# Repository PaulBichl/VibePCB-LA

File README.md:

# VibePCB logic analyzer

A 16-channel, 100 MSa/s USB 2.0 HS logic analyzer: a **Lattice ECP5 FPGA (CABGA-256 BGA)**
capturing into a **32 MB SDRAM (54-ball BGA)**, read out over an **FT2232H**. 98 x 64 mm, 6 layers.
Designed with [VibePCB](https://github.com/PaulBichl/vibepcb) (tscircuit -> KiCad) as a stretch of
the tooling: two 0.8 mm BGAs escaped and routed by VibePCB's own router, a length-checked 39-signal
memory bus, a coupled 90 ohm USB pair, three power planes.

Status: passes `check` (KiCad DRC and ERC with 0 errors, house rules). Not fabricated yet.

## Look at it

| | |
|---|---|
| Schematic | [PDF](boards/la-ecp5/hardware/la-ecp5-schematic.pdf) |
| Layout | [PDF, one page per copper layer](boards/la-ecp5/hardware/la-ecp5-layout.pdf), [front](boards/la-ecp5/hardware/la-ecp5-layout-front.svg), [back](boards/la-ecp5/hardware/la-ecp5-layout-back.svg) |
| 3D | [top](boards/la-ecp5/hardware/la-ecp5-top.png), [bottom](boards/la-ecp5/hardware/la-ecp5-bottom.png) |
| BOM (LCSC / MPN) | [CSV](boards/la-ecp5/hardware/la-ecp5-bom.csv) |
| KiCad project | [kicad/](boards/la-ecp5/hardware/kicad) |
| Source | [index.circuit.tsx](boards/la-ecp5/index.circuit.tsx) (tscircuit), [vibepcb.toml](boards/la-ecp5/vibepcb.toml) (rules, planes, length groups, BGA escape), [routes.toml](boards/la-ecp5/routes.toml) (routing order) |

The KiCad project opens as it is. The 3D models are left out because they are tens of MB;
`pcb fix` downloads them. Gerbers and pick-and-place files are not in the repo: either plot them
from the KiCad project, or build the board (below) and run `hatch run pcb fab la-ecp5`, which
writes Gerbers, drill, BOM, CPL and a JLCPCB upload set.

## Target spec

| | |
|---|---|
| Channels | 16, two banks of 8, threshold per bank (I/O rail 1.2-5 V, threshold ~ rail / 2) |
| Sample rate | 100 MSa/s x 16 into SDRAM |
| Buffer | 32 MB (256 Mbit 16-bit SDR SDRAM) = 16 M samples x 16 ch |
| Streaming | ~40 MB/s over USB 2.0 HS (FT2232H sync FIFO): 16 ch at ~20 MSa/s |
| Inputs | 1 Mohm, 1k series + SRV05-4 clamps to the bank rail / GND |
| Probe | 2x10 2.54 mm header (16 signals + 4 GND), labelled per pin |
| Power | USB-C 5 V, < 3 W |
| Debug | JTAG header (J5), 3 LEDs (power, activity, trigger) |

## How it works

```
 probe     +--------------+    +---------------+    +-------------+
 header -->| 1k, 1M,      |--->| 74LVC8T245 x2 |--->|             |<--- 100 MHz osc
 16 ch     | SRV05-4      |    | level shift   |    |  ECP5-25F   |
           +--------------+    +---------------+    |  CABGA-256  |<==> IS42S16160J SDRAM
                  ^                    ^            |             |     (32 MB, BGA-54)
                  +--- bank rail ------+            |             |
                       1.2-5 V, x2                  |             |<--- JTAG (J5)
                          ^                         |             |
               TLV9062 + RC filter <------ PWM -----|             |
                                                    +--+-------+--+
                                                       ^       ^
                                    W25Q128 -----------+       | 8-bit sync FIFO
                                    config flash               v
                                       ^  SPI (ch B)     +---------+  USB 2.0 HS  +------------+
                                       +-----------------| FT2232H |<============>| USB-C, ESD |
                                                         +---------+              +-----+------+
                                                                                        | 5 V
                                           3.3 V, 1.1 V, 2.5 V <--- TLV62569 x3 <-------+
```

**Signal path.** A probe signal enters the 2x10 header, passes a 1k series resistor (with the
SRV05-4 clamping it to the bank rail and GND, and 1M pulling an open input low) and reaches a
74LVC8T245. Its A side runs on the bank rail, so the input threshold follows that rail (~ rail / 2);
its B side runs on 3.3 V and drives the FPGA. One translator per bank of 8 channels, so two target
logic families can be probed at once.

**Threshold.** The FPGA sets each bank rail itself: a PWM pin, a 10k / 1 uF RC filter, a TLV9062
op-amp with gain 1.5 -> 1.2 to 4.95 V. No DAC chip needed.

**Capture.** The FPGA samples all 16 inputs at 100 MHz (from the oscillator on a primary clock
input), runs the trigger logic and writes the samples to the SDRAM: 16 bit x 100 MSa/s = 200 MB/s,
which the 16-bit SDRAM (-7 grade, rated to 143 MHz) takes in bursts; 32 MB = 16 M samples (0.16 s at
full rate).

**Readout.** The FT2232H is the USB 2.0 high-speed interface: channel A is an 8-bit synchronous
FIFO to the FPGA (~40 MB/s, its 60 MHz CLKOUT on a primary clock input), enough to read the buffer
out or to stream 16 ch at ~20 MSa/s live. Channel B (MPSSE) writes the FPGA bitstream into the
W25Q128 SPI flash while it holds PROGRAMN low; the FPGA boots from it in master SPI mode
(CFG[2:0] = 010), so no separate programmer is needed. The 93LC56 EEPROM stores the FT2232H's
FIFO-mode setting.

**Power.** USB-C 5 V (5.1k CC pull-downs, no PD) -> three TLV62569 bucks: 3.3 V for I/O, SDRAM and
USB, 1.1 V for the FPGA core, 2.5 V for its aux supply. Under 3 W.

**Why this FPGA.** The ECP5 LFE5U-25F has 24k LUTs, 1 Mbit of block RAM and plenty of I/O for 16
inputs + the 39-signal SDRAM bus + the FIFO, with a fully open toolchain (yosys / nextpnr-ecp5 /
Project Trellis). Its block RAM alone would only hold ~60 k samples, hence the SDRAM. The CABGA-256
package was the point of the exercise: an earlier version of this board used an iCE40HX4K in a
TQFP-144 (4 layers, in git history) because tscircuit's router could not escape a BGA; VibePCB now
does the escape and routing itself.

## Layout

- **Stack-up (6 layers):** top signals + GND / In1 GND / In2 1.1 V core / In3 3.3 V IO /
  In4 GND / bottom signals + GND. Each power ball or pad gets its own via to its plane.
- **BGA escape:** both ball grids are escaped by VibePCB (0.1 mm tracks between the 0.36 mm balls
  at 0.8 mm pitch, dogbone vias 0.4 / 0.2 mm, mechanically drilled; deeper balls out on the
  bottom layer).
- **Planar pin plan:** FPGA pins are assigned by package side so no routes cross: inputs and the
  100 MHz clock west, SDRAM east, FT2232H FIFO north, configuration SPI south. Within a side, signals
  pair with balls by angle around both parts, so the routes nest instead of crossing.
- **SDRAM bus:** two length groups (data, address / control), skew <= 45 mm (~0.3 ns, ~10 % of
  the read window at 100 MHz), checked by KiCad.
- **USB:** a 90 ohm differential pair from the ESD part to the FT2232H, coupled over 7.3 mm with
  +0.09 mm skew.

Net classes, the USB pair, the length groups, the planes and the escape settings live in
[`boards/la-ecp5/vibepcb.toml`](boards/la-ecp5/vibepcb.toml); the routing order in
[`routes.toml`](boards/la-ecp5/routes.toml).

## Parts (JLCPCB / LCSC)

| Part | LCSC |
|------|------|
| LFE5U-25F-7BG256I (FPGA) | C1550762 |
| IS42S16160J-7BLI (SDRAM) | C1348766 |
| FT2232HL (USB) | C27882 |
| SN74LVC8T245PWR | C27643 |
| W25Q128JVSIQ (config flash) | C97521 |
| 93LC56BT-I/OT | C190271 |
| SX3M100.000B20F30TNN (100 MHz osc) | C5179979 |
| X322512MSB4SI (12 MHz crystal) | C9002 |
| TLV62569DBVR | C141836 |
| TLV9062IDR | C398355 |
| USBLC6-2SC6 | C7519 |
| SRV05-4 | C2836319 |
| TYPE-C-31-M-12 | C165948 |

Passives are in the [BOM](boards/la-ecp5/hardware/la-ecp5-bom.csv). Check stock before
ordering.

## Setup / build

Clone [`vibepcb`](https://github.com/PaulBichl/vibepcb) next to this repo as `VibePCB`, then

```bash
hatch run setup
hatch run pcb all la-ecp5       # build, fix, route, check
hatch run pcb publish la-ecp5   # refresh boards/la-ecp5/hardware/
hatch run pcb fab la-ecp5       # Gerbers, drill, BOM, CPL
```

`package.json` pins the tscircuit version the board was built with, because routing differs
between versions.

Out of scope for this repo: FPGA gateware and the host software (a sigrok driver).

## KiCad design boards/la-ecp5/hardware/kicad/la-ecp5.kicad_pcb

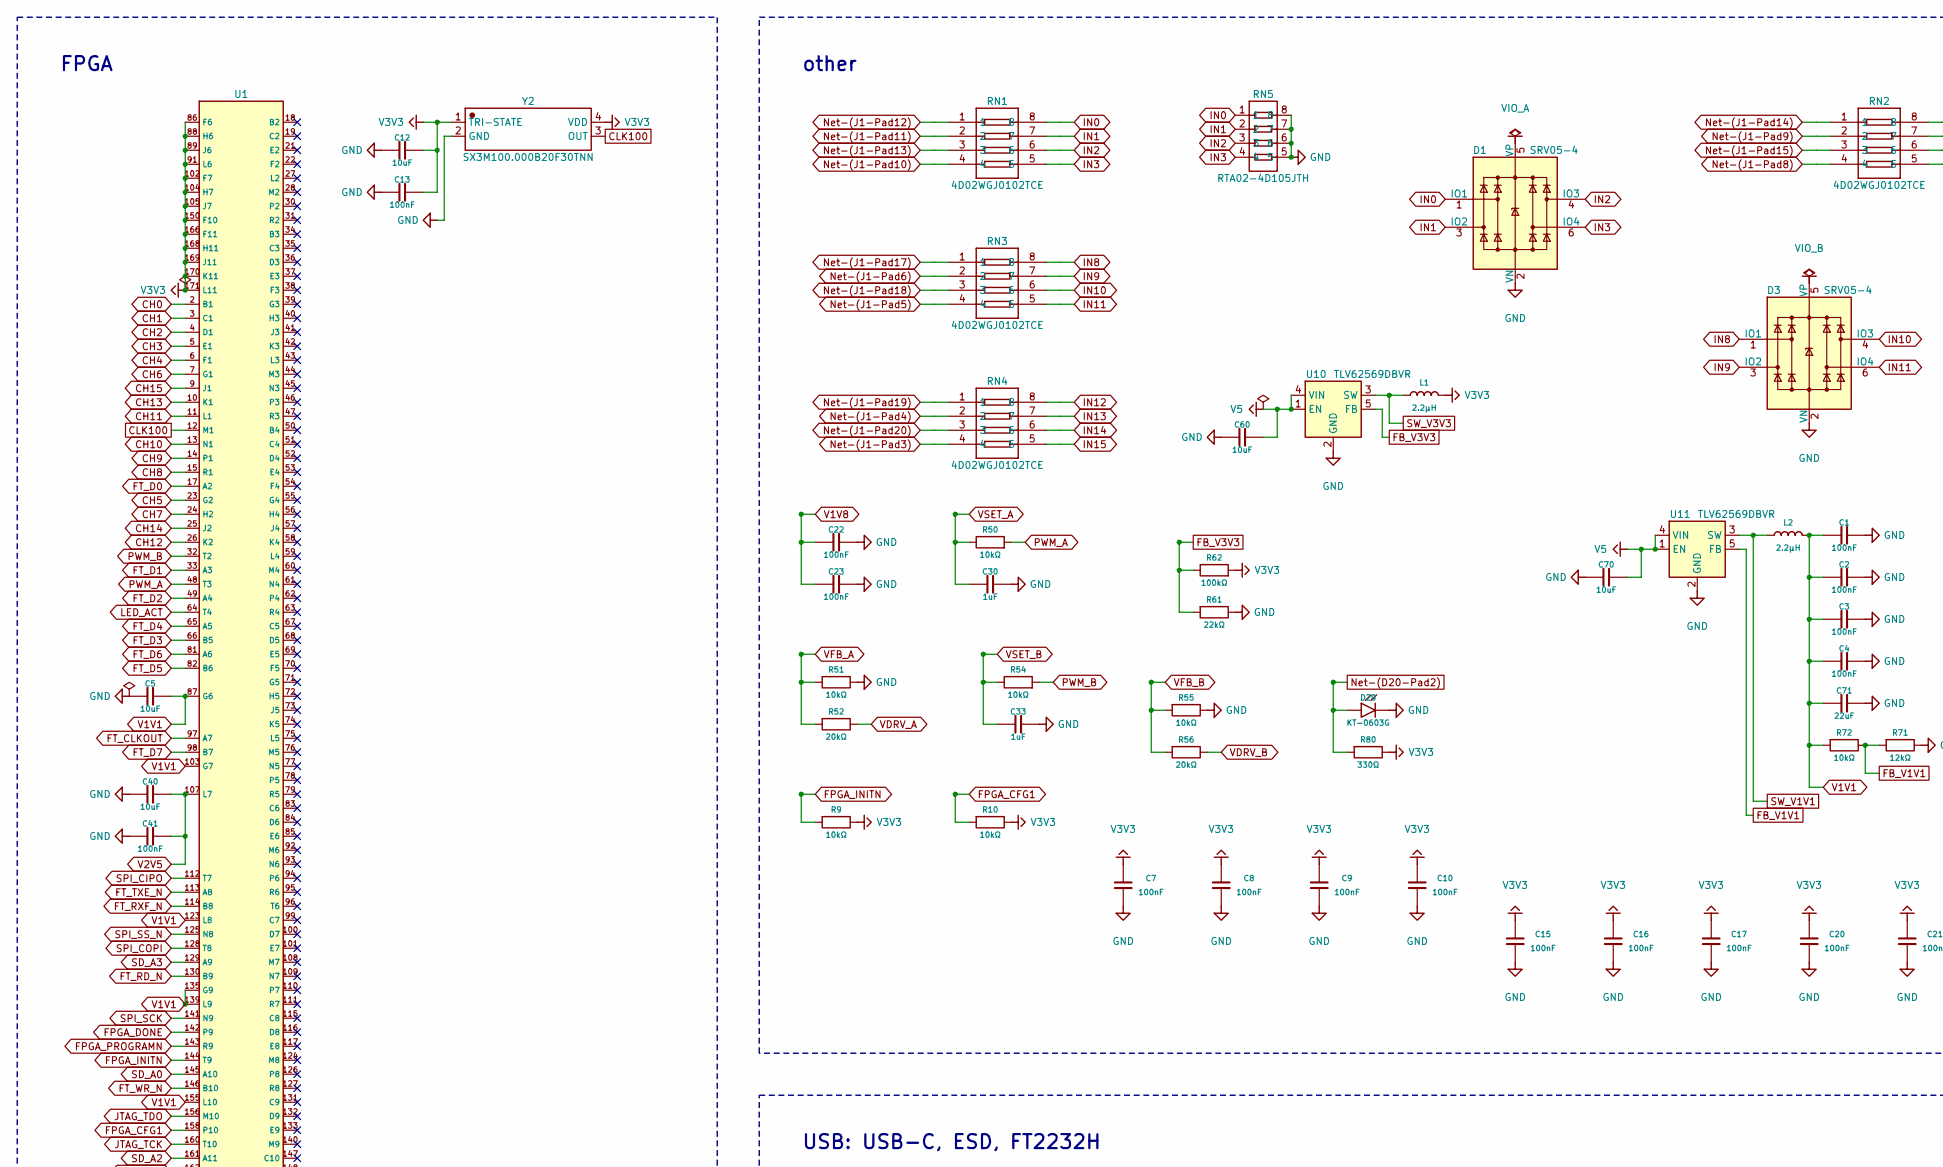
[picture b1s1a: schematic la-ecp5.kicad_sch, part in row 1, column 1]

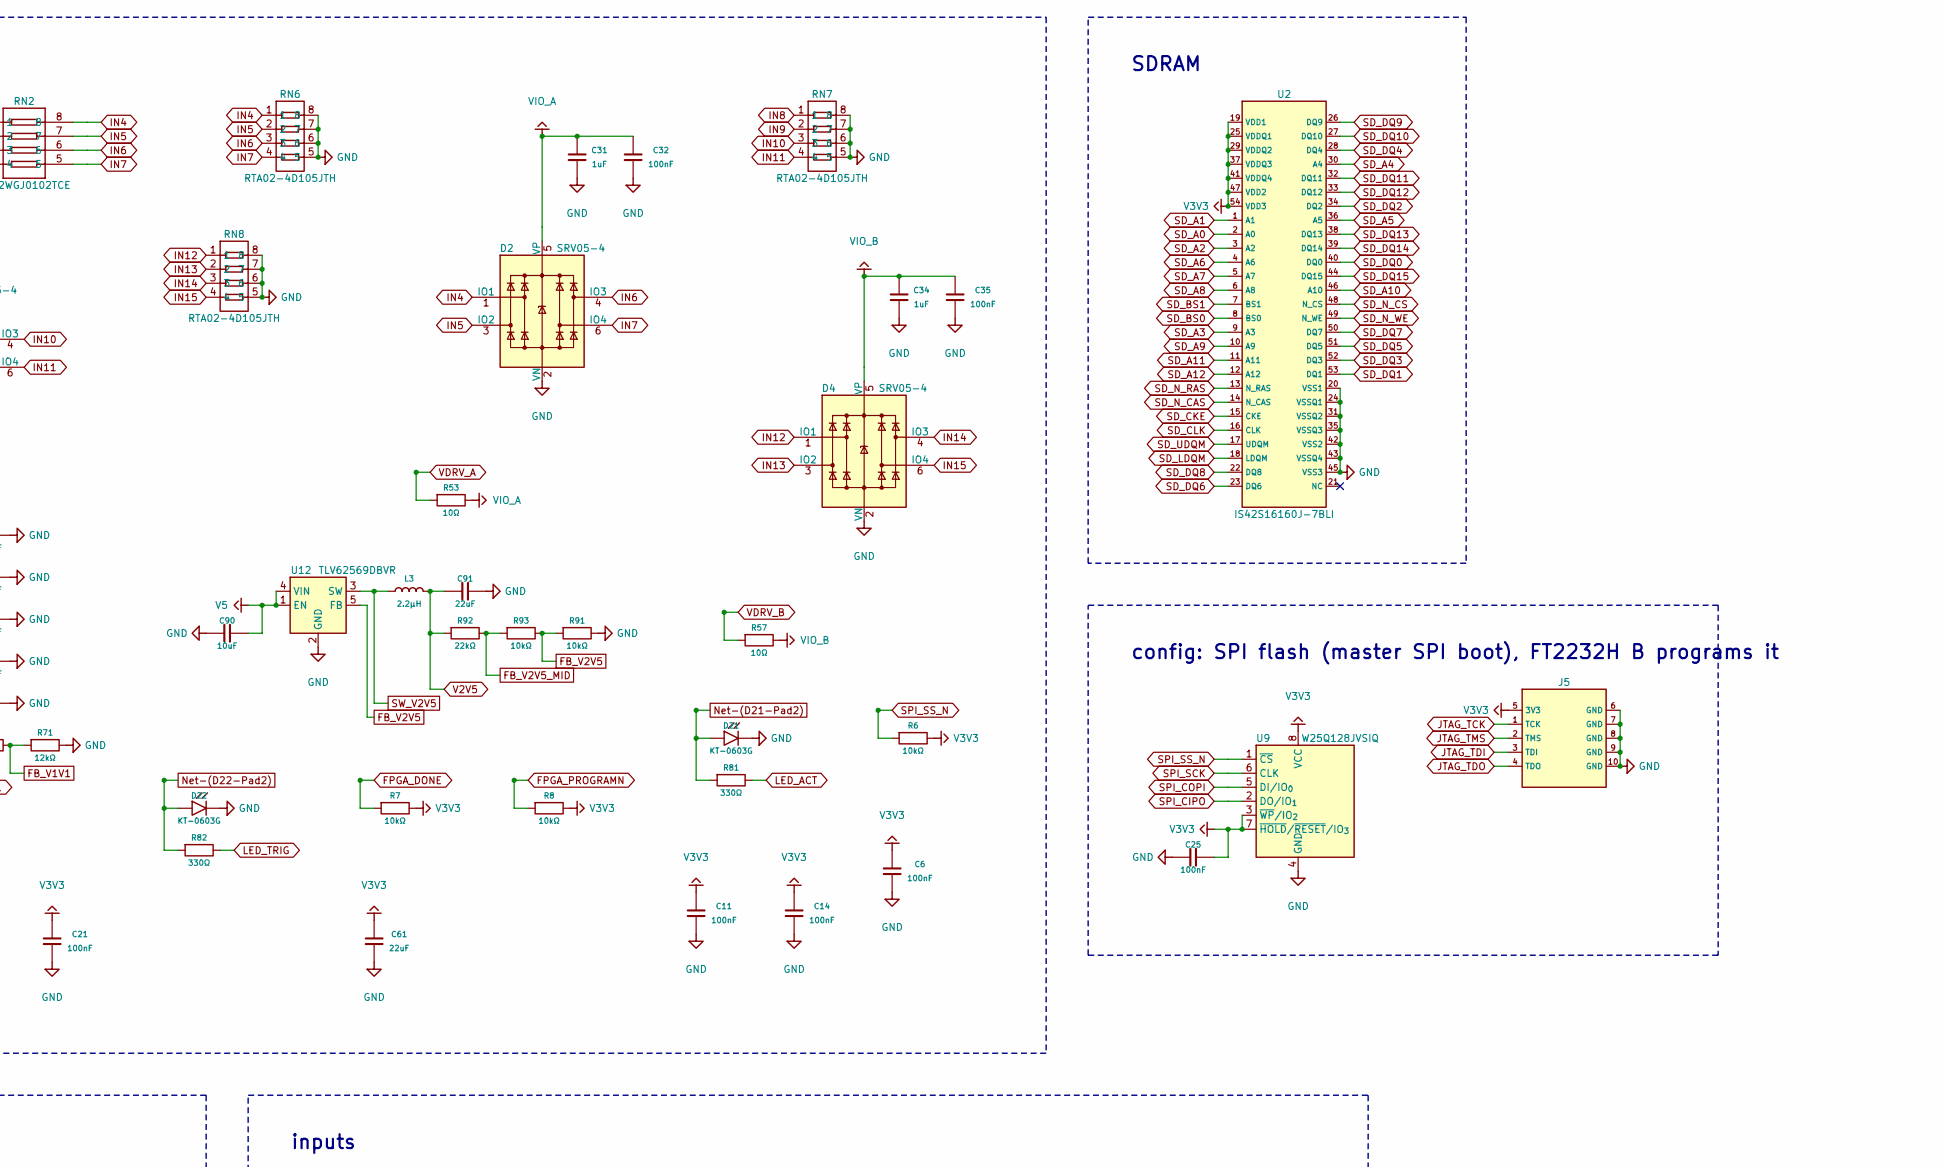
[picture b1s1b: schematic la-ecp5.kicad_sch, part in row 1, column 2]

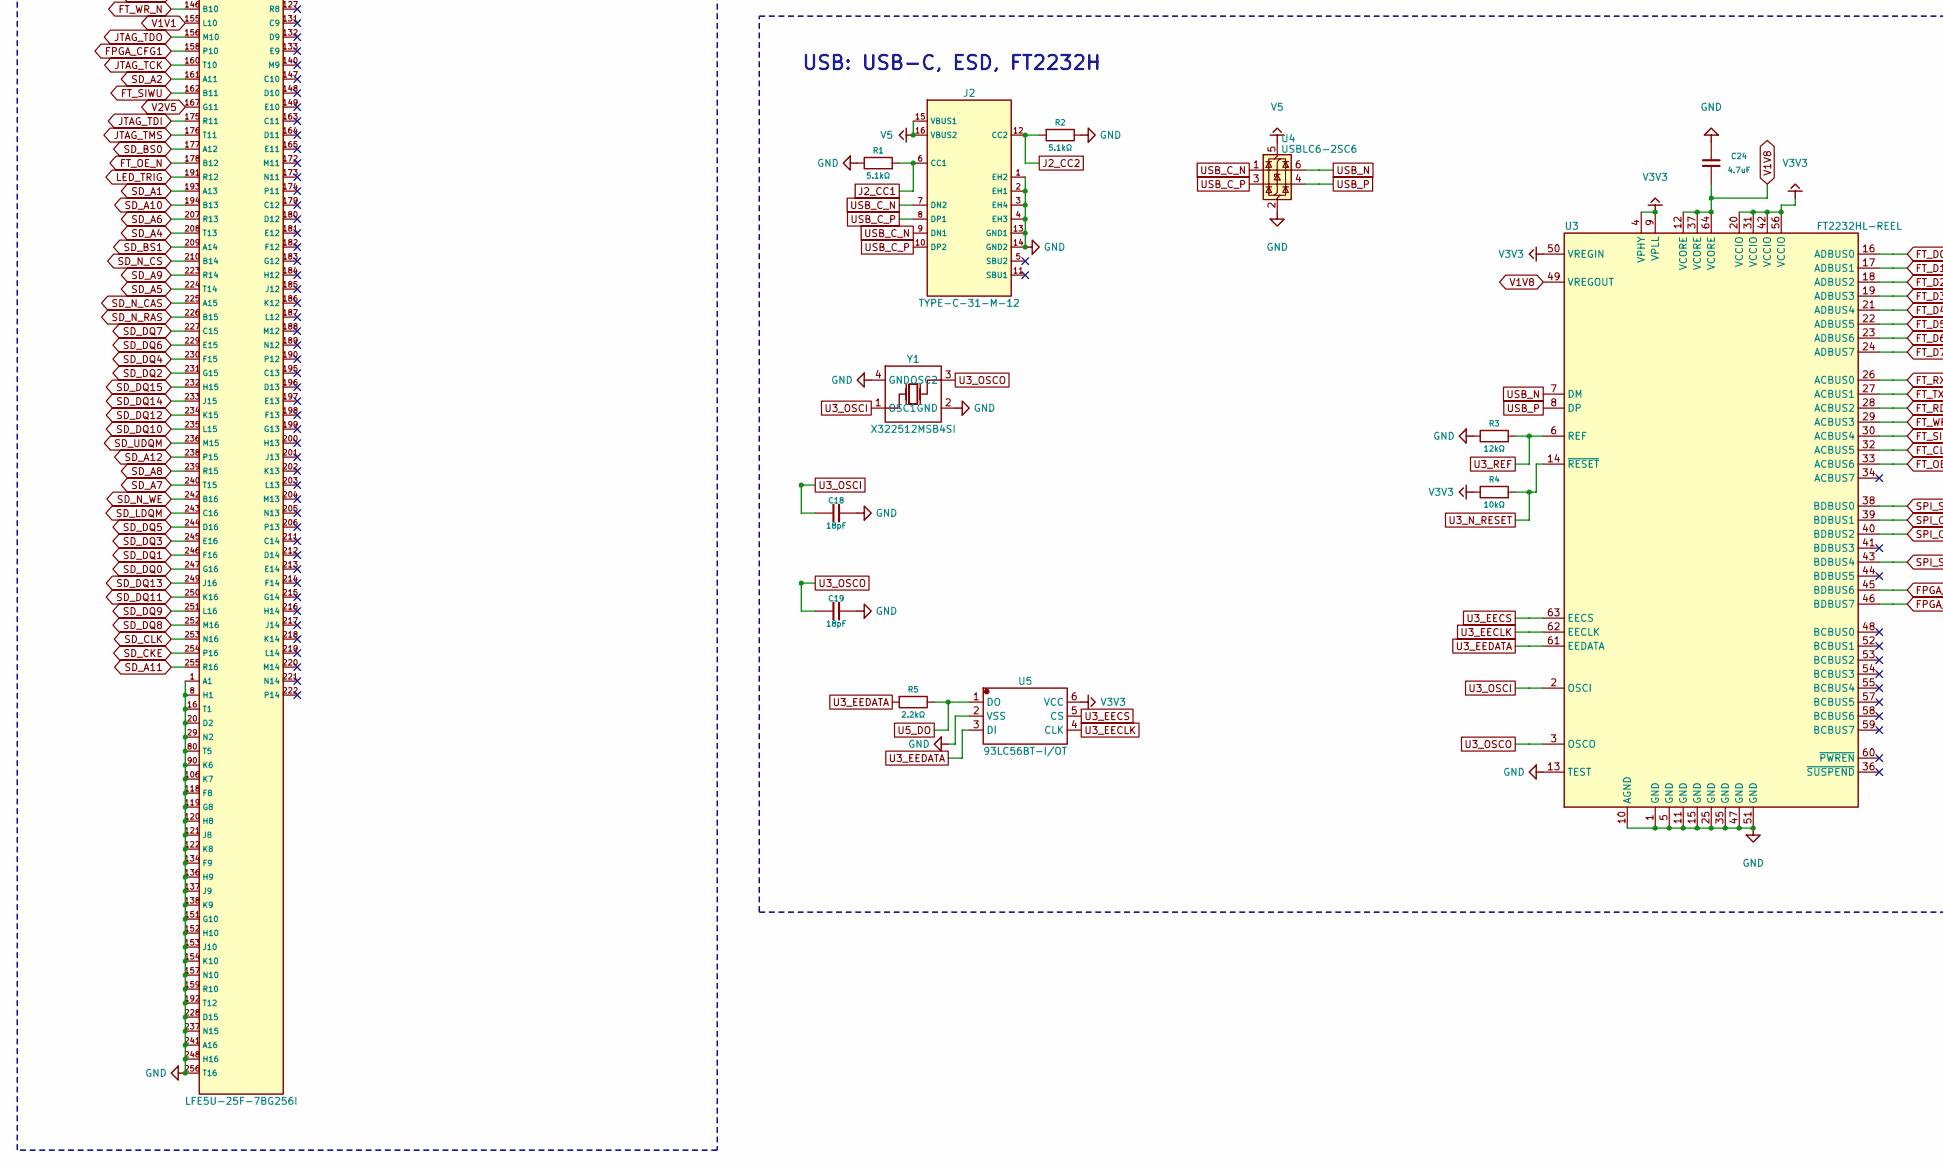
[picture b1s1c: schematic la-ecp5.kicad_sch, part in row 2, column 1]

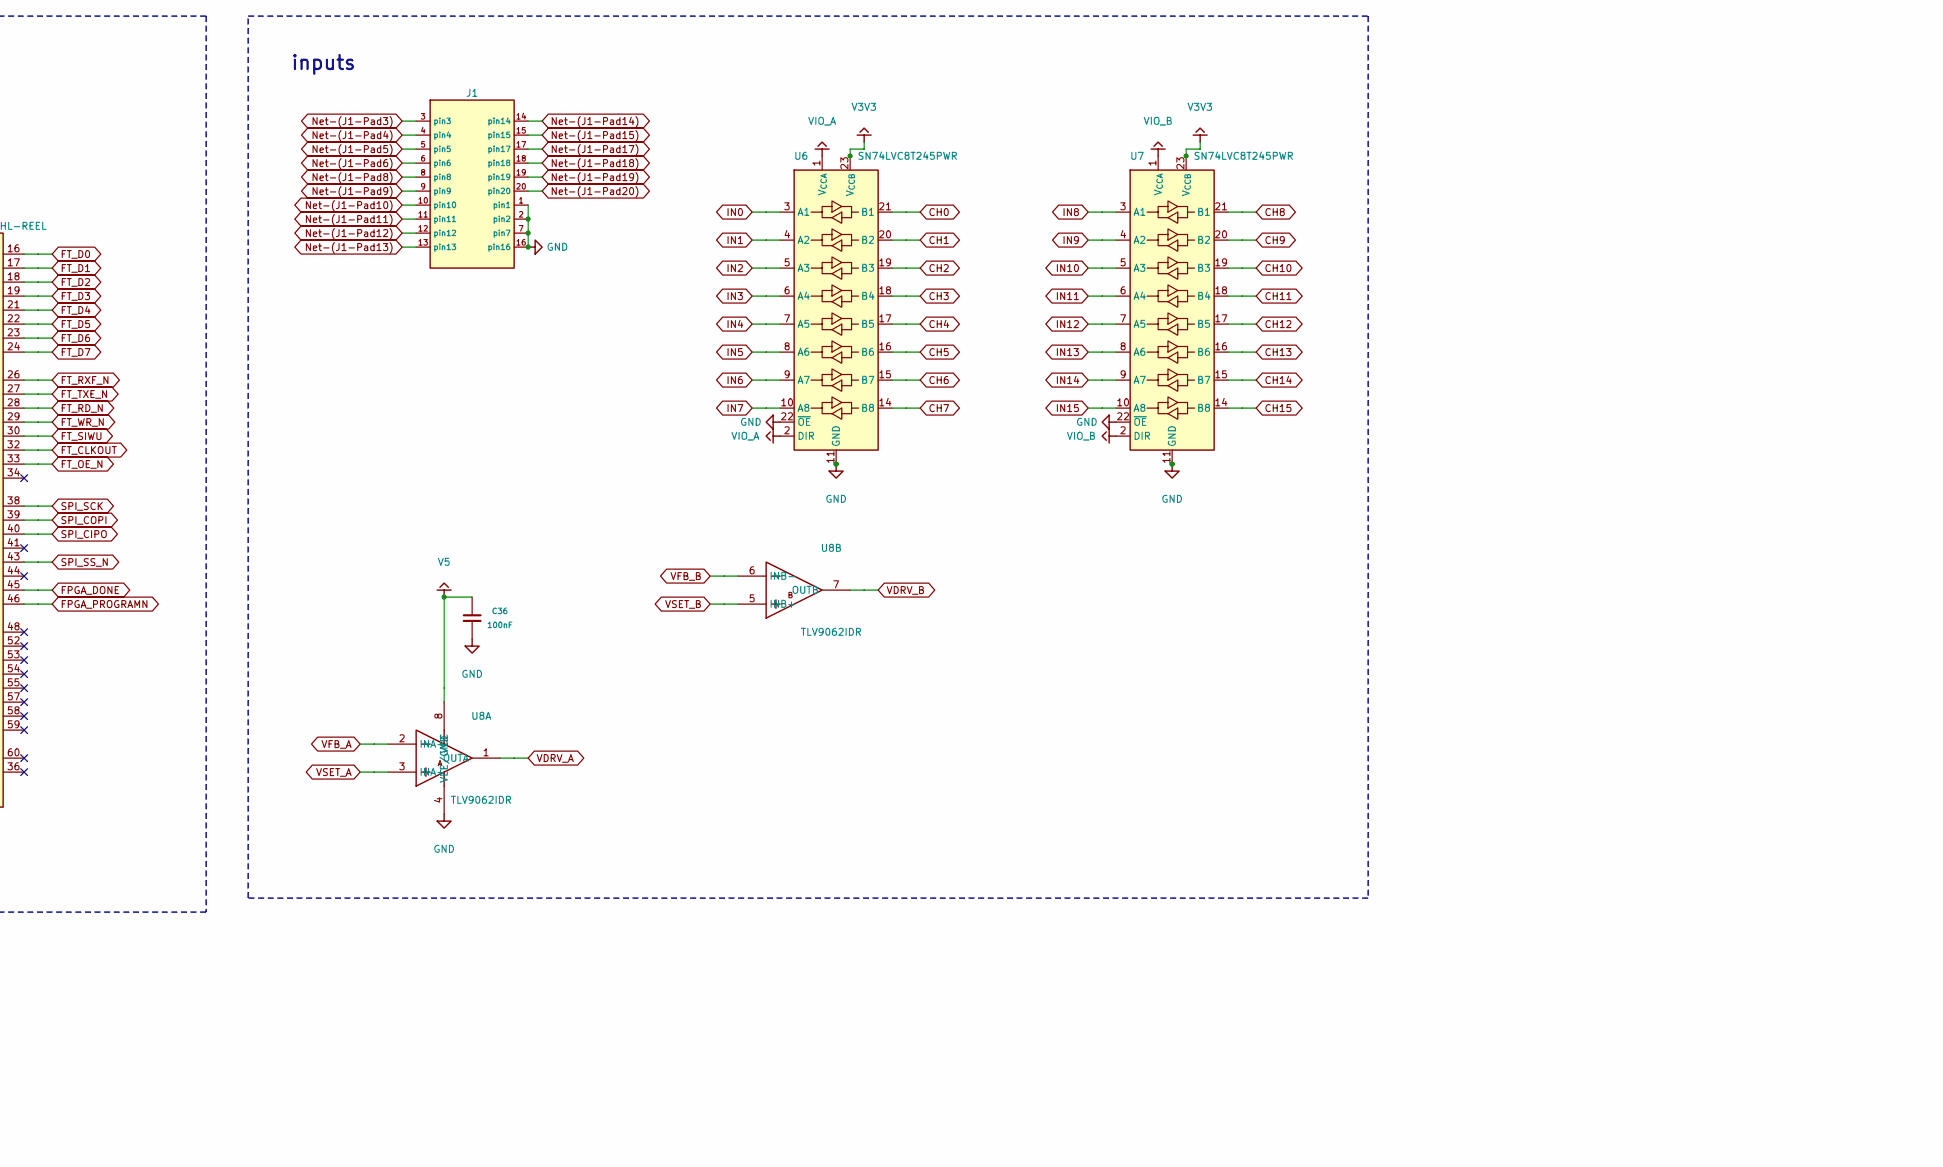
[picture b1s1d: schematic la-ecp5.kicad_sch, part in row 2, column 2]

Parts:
C1, C2, C3, C4, C6, C7, C8, C9, C10, C11, C13, C14, C15, C16, C17, C20, C21, C22, C23, C25, C32, C35, C36, C41: 100nF; capacitor_cap0402; LCSC C1525
C5, C12, C40, C60, C70, C90: 10uF; capacitor_cap0603; LCSC C19702
C18, C19: 18pF; capacitor_cap0402; LCSC C1549
C24: 4.7uF; capacitor_cap0603; LCSC C19666
C30, C31, C33, C34: 1uF; capacitor_cap0402; LCSC C52923
C61, C71, C91: 22uF; capacitor_cap0805; LCSC C45783
D1, D2, D3, D4: SRV05-4; MPN SRV05-4; LCSC C2836319
D20, D21, D22: KT-0603G; MPN KT-0603G; LCSC C12624
J1: pin_header_pinrow20_p2_54_nopinlabels_rows2
J2: TYPE-C-31-M-12; MPN TYPE-C-31-M-12; LCSC C165948
J5: pin_header_pinrow10_p2_54_rows2
L1, L2, L3: 2.2µH; inductor_0805; LCSC C63167
R1, R2: 5.1kΩ; resistor_res0402; LCSC C25905
R3, R71: 12kΩ; resistor_res0402; LCSC C25752
R4, R6, R7, R8, R9, R10, R50, R51, R54, R55, R72, R91, R93: 10kΩ; resistor_res0402; LCSC C25744
R5: 2.2kΩ; resistor_res0402; LCSC C25879
R52, R56: 20kΩ; resistor_res0402; LCSC C25765
R53, R57: 10Ω; resistor_res0402; LCSC C25077
R61, R92: 22kΩ; resistor_res0402; LCSC C25768
R62: 100kΩ; resistor_res0402; LCSC C25741
R80, R81, R82: 330Ω; resistor_res0402; LCSC C25104
RN1, RN2, RN3, RN4: 4D02WGJ0102TCE; MPN 4D02WGJ0102TCE; LCSC C25726
RN5, RN6, RN7, RN8: RTA02-4D105JTH; MPN RTA02-4D105JTH; LCSC C458532
U1: LFE5U-25F-7BG256I; MPN LFE5U-25F-7BG256I; LCSC C1550762
U2: IS42S16160J-7BLI; MPN IS42S16160J-7BLI; LCSC C1348766
U3: FT2232HL-REEL; MPN FT2232HL-REEL; LCSC C27882
U4: USBLC6-2SC6; MPN USBLC6-2SC6; LCSC C7519
U5: 93LC56BT-I/OT; 93LC56BT-I_OT; MPN 93LC56BT-I/OT; LCSC C190271
U6, U7: SN74LVC8T245PWR; MPN SN74LVC8T245PWR; LCSC C27643
U8: TLV9062IDR; MPN TLV9062IDR; LCSC C398355
U9: W25Q128JVSIQ; MPN W25Q128JVSIQ; LCSC C97521
U10, U11, U12: TLV62569DBVR; MPN TLV62569DBVR; LCSC C141836
Y1: X322512MSB4SI; MPN X322512MSB4SI; LCSC C9002
Y2: SX3M100.000B20F30TNN; SX3M100_000B20F30TNN; MPN SX3M100.000B20F30TNN; LCSC C5179979

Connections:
CH0: U1.2 (B1), U6.21 (B1)
CH1: U1.3 (C1), U6.20 (B2)
CH2: U1.4 (D1), U6.19 (B3)
CH3: U1.5 (E1), U6.18 (B4)
CH4: U1.6 (F1), U6.17 (B5)
CH5: U1.23 (G2), U6.16 (B6)
CH6: U1.7 (G1), U6.15 (B7)
CH7: U1.24 (H2), U6.14 (B8)
CH8: U1.15 (R1), U7.21 (B1)
CH9: U1.14 (P1), U7.20 (B2)
CH10: U1.13 (N1), U7.19 (B3)
CH11: U1.11 (L1), U7.18 (B4)
CH12: U1.26 (K2), U7.17 (B5)
CH13: U1.10 (K1), U7.16 (B6)
CH14: U1.25 (J2), U7.15 (B7)
CH15: U1.9 (J1), U7.14 (B8)
CLK100: U1.12 (M1), Y2.3 (OUT)
FB_V1V1: R71.1, R72.2, U11.5 (FB)
FB_V2V5: R91.1, R93.2, U12.5 (FB)
FB_V2V5_MID: R92.2, R93.1
FB_V3V3: R61.1, R62.2, U10.5 (FB)
FPGA_CFG1: R10.1, U1.158 (P10)
FPGA_DONE: R7.1, U1.142 (P9), U3.45 (BDBUS6)
FPGA_INITN: R9.1, U1.144 (T9)
FPGA_PROGRAMN: R8.1, U1.143 (R9), U3.46 (BDBUS7)
FT_CLKOUT: U1.97 (A7), U3.32 (ACBUS5)
FT_D0: U1.17 (A2), U3.16 (ADBUS0)
FT_D1: U1.33 (A3), U3.17 (ADBUS1)
FT_D2: U1.49 (A4), U3.18 (ADBUS2)
FT_D3: U1.66 (B5), U3.19 (ADBUS3)
FT_D4: U1.65 (A5), U3.21 (ADBUS4)
FT_D5: U1.82 (B6), U3.22 (ADBUS5)
FT_D6: U1.81 (A6), U3.23 (ADBUS6)
FT_D7: U1.98 (B7), U3.24 (ADBUS7)
FT_OE_N: U1.178 (B12), U3.33 (ACBUS6)
FT_RD_N: U1.130 (B9), U3.28 (ACBUS2)
FT_RXF_N: U1.114 (B8), U3.26 (ACBUS0)
FT_SIWU: U1.162 (B11), U3.30 (ACBUS4)
FT_TXE_N: U1.113 (A8), U3.27 (ACBUS1)
FT_WR_N: U1.146 (B10), U3.29 (ACBUS3)
GND: C1.2, C2.2, C3.2, C4.2, C5.2, C6.2, C7.2, C8.2, C9.2, C10.2, C11.2, C12.2, C13.2, C14.2, C15.2, C16.2, C17.2, C18.2, C19.2, C20.2, C21.2, C22.2, C23.2, C24.2, C25.2, C30.2, C31.2, C32.2, C33.2, C34.2, C35.2, C36.2, C40.2, C41.2, C60.2, C61.2, C70.2, C71.2, C90.2, C91.2, D1.2 (VN), D2.2 (VN), D3.2 (VN), D4.2 (VN), D20.1 (cathode), D21.1 (cathode), D22.1 (cathode), J1.1, J1.2, J1.7, J1.16, J2.1 (EH2), J2.2 (EH1), J2.3 (EH4), J2.4 (EH3), J2.13 (GND1), J2.14 (GND2), J5.6 (GND), J5.7 (GND), J5.8 (GND), J5.9 (GND), J5.10 (GND), R1.2, R2.2, R3.2, R51.2, R55.2, R61.2, R71.2, R91.2, RN5.5, RN5.6, RN5.7, RN5.8, RN6.5, RN6.6, RN6.7, RN6.8, RN7.5, RN7.6, RN7.7, RN7.8, RN8.5, RN8.6, RN8.7, RN8.8, U1.1 (A1), U1.8 (H1), U1.16 (T1), U1.20 (D2), U1.29 (N2), U1.80 (T5), U1.90 (K6), U1.106 (K7), U1.118 (F8), U1.119 (G8), U1.120 (H8), U1.121 (J8), U1.122 (K8), U1.134 (F9), U1.136 (H9), U1.137 (J9), U1.138 (K9), U1.151 (G10), U1.152 (H10), U1.153 (J10), U1.154 (K10), U1.157 (N10), U1.159 (R10), U1.192 (T12), U1.228 (D15), U1.237 (N15), U1.241 (A16), U1.248 (H16), U1.256 (T16), U2.20 (VSS1), U2.24 (VSSQ1), U2.31 (VSSQ2), U2.35 (VSSQ3), U2.42 (VSS2), U2.43 (VSSQ4), U2.45 (VSS3), U3.1 (GND), U3.5 (GND), U3.10 (AGND), U3.11 (GND), U3.13 (TEST), U3.15 (GND), U3.25 (GND), U3.35 (GND), U3.47 (GND), U3.51 (GND), U4.2 (GND), U5.2 (VSS), U6.11 (GND), U6.12 (GND), U6.13 (GND), U6.22 (~OE), U7.11 (GND), U7.12 (GND), U7.13 (GND), U7.22 (~OE), U8.4 (VEE/GND), U9.4 (GND), U10.2 (GND), U11.2 (GND), U12.2 (GND), Y1.2 (GND), Y1.4 (GND), Y2.2 (GND)
IN0: D1.1 (IO1), RN1.8, RN5.1, U6.3 (A1)
IN1: D1.3 (IO2), RN1.7, RN5.2, U6.4 (A2)
IN2: D1.4 (IO3), RN1.6, RN5.3, U6.5 (A3)
IN3: D1.6 (IO4), RN1.5, RN5.4, U6.6 (A4)
IN4: D2.1 (IO1), RN2.8, RN6.1, U6.7 (A5)
IN5: D2.3 (IO2), RN2.7, RN6.2, U6.8 (A6)
IN6: D2.4 (IO3), RN2.6, RN6.3, U6.9 (A7)
IN7: D2.6 (IO4), RN2.5, RN6.4, U6.10 (A8)
IN8: D3.1 (IO1), RN3.8, RN7.1, U7.3 (A1)
IN9: D3.3 (IO2), RN3.7, RN7.2, U7.4 (A2)
IN10: D3.4 (IO3), RN3.6, RN7.3, U7.5 (A3)
IN11: D3.6 (IO4), RN3.5, RN7.4, U7.6 (A4)
IN12: D4.1 (IO1), RN4.8, RN8.1, U7.7 (A5)
IN13: D4.3 (IO2), RN4.7, RN8.2, U7.8 (A6)
IN14: D4.4 (IO3), RN4.6, RN8.3, U7.9 (A7)
IN15: D4.6 (IO4), RN4.5, RN8.4, U7.10 (A8)
J2_CC1: J2.6 (CC1), R1.1
J2_CC2: J2.12 (CC2), R2.1
JTAG_TCK: J5.1 (TCK), U1.160 (T10)
JTAG_TDI: J5.3 (TDI), U1.175 (R11)
JTAG_TDO: J5.4 (TDO), U1.156 (M10)
JTAG_TMS: J5.2 (TMS), U1.176 (T11)
LED_ACT: R81.2, U1.64 (T4)
LED_TRIG: R82.2, U1.191 (R12)
unnamed: D20.2 (anode), R80.1
unnamed: D21.2 (anode), R81.1
unnamed: D22.2 (anode), R82.1
unnamed: J1.3, RN4.4
unnamed: J1.4, RN4.2
unnamed: J1.5, RN3.4
unnamed: J1.6, RN3.2
unnamed: J1.8, RN2.4
unnamed: J1.9, RN2.2
unnamed: J1.10, RN1.4
unnamed: J1.11, RN1.2
unnamed: J1.12, RN1.1
unnamed: J1.13, RN1.3
unnamed: J1.14, RN2.1
unnamed: J1.15, RN2.3
unnamed: J1.17, RN3.1
unnamed: J1.18, RN3.3
unnamed: J1.19, RN4.1
unnamed: J1.20, RN4.3
PWM_A: R50.1, U1.48 (T3)
PWM_B: R54.1, U1.32 (T2)
SD_A0: U1.145 (A10), U2.2 (A0)
SD_A1: U1.193 (A13), U2.1 (A1)
SD_A2: U1.161 (A11), U2.3 (A2)
SD_A3: U1.129 (A9), U2.9 (A3)
SD_A4: U1.208 (T13), U2.30 (A4)
SD_A5: U1.224 (T14), U2.36 (A5)
SD_A6: U1.207 (R13), U2.4 (A6)
SD_A7: U1.240 (T15), U2.5 (A7)
SD_A8: U1.239 (R15), U2.6 (A8)
SD_A9: U1.223 (R14), U2.10 (A9)
SD_A10: U1.194 (B13), U2.46 (A10)
SD_A11: U1.255 (R16), U2.11 (A11)
SD_A12: U1.238 (P15), U2.12 (A12)
SD_BS0: U1.177 (A12), U2.8 (BS0)
SD_BS1: U1.209 (A14), U2.7 (BS1)
SD_CKE: U1.254 (P16), U2.15 (CKE)
SD_CLK: U1.253 (N16), U2.16 (CLK)
SD_DQ0: U1.247 (G16), U2.40 (DQ0)
SD_DQ1: U1.246 (F16), U2.53 (DQ1)
SD_DQ2: U1.231 (G15), U2.34 (DQ2)
SD_DQ3: U1.245 (E16), U2.52 (DQ3)
SD_DQ4: U1.230 (F15), U2.28 (DQ4)
SD_DQ5: U1.244 (D16), U2.51 (DQ5)
SD_DQ6: U1.229 (E15), U2.23 (DQ6)
SD_DQ7: U1.227 (C15), U2.50 (DQ7)
SD_DQ8: U1.252 (M16), U2.22 (DQ8)
SD_DQ9: U1.251 (L16), U2.26 (DQ9)
SD_DQ10: U1.235 (L15), U2.27 (DQ10)
SD_DQ11: U1.250 (K16), U2.32 (DQ11)
SD_DQ12: U1.234 (K15), U2.33 (DQ12)
SD_DQ13: U1.249 (J16), U2.38 (DQ13)
SD_DQ14: U1.233 (J15), U2.39 (DQ14)
SD_DQ15: U1.232 (H15), U2.44 (DQ15)
SD_LDQM: U1.243 (C16), U2.18 (LDQM)
SD_N_CAS: U1.225 (A15), U2.14 (N_CAS)
SD_N_CS: U1.210 (B14), U2.48 (N_CS)
SD_N_RAS: U1.226 (B15), U2.13 (N_RAS)
SD_N_WE: U1.242 (B16), U2.49 (N_WE)
SD_UDQM: U1.236 (M15), U2.17 (UDQM)
SW_V1V1: L2.1, U11.3 (SW)
SW_V2V5: L3.1, U12.3 (SW)
SW_V3V3: L1.1, U10.3 (SW)
U3_EECLK: U3.62 (EECLK), U5.4 (CLK)
U3_EECS: U3.63 (EECS), U5.5 (CS)
U3_EEDATA: R5.1, U3.61 (EEDATA), U5.3 (DI)
U3_N_RESET: R4.1, U3.14 (~RESET)
U3_OSCI: C18.1, U3.2 (OSCI), Y1.1 (OSC1)
U3_OSCO: C19.1, U3.3 (OSCO), Y1.3 (OSC2)
U3_REF: R3.1, U3.6 (REF)
U5_DO: R5.2, U5.1 (DO)
USB_C_N: J2.7 (DN2), J2.9 (DN1), U4.1 (I/O1)
USB_C_P: J2.8 (DP1), J2.10 (DP2), U4.3 (I/O2)
USB_N: U3.7 (DM), U4.6 (I/O1)
USB_P: U3.8 (DP), U4.4 (I/O2)
V1V1: C1.1, C2.1, C3.1, C4.1, C5.1, C71.1, L2.2, R72.1, U1.87 (G6), U1.103 (G7), U1.123 (L8), U1.135 (G9), U1.139 (L9), U1.155 (L10)
V1V8: C22.1, C23.1, C24.1, U3.12 (VCORE), U3.37 (VCORE), U3.49 (VREGOUT), U3.64 (VCORE)
V2V5: C40.1, C41.1, C91.1, L3.2, R92.1, U1.107 (L7), U1.167 (G11)
V3V3: C6.1, C7.1, C8.1, C9.1, C10.1, C11.1, C12.1, C13.1, C14.1, C15.1, C16.1, C17.1, C20.1, C21.1, C25.1, C61.1, J5.5 (3V3), L1.2, R4.2, R6.2, R7.2, R8.2, R9.2, R10.2, R62.1, R80.2, U1.86 (F6), U1.88 (H6), U1.89 (J6), U1.91 (L6), U1.102 (F7), U1.104 (H7), U1.105 (J7), U1.150 (F10), U1.166 (F11), U1.168 (H11), U1.169 (J11), U1.170 (K11), U1.171 (L11), U2.19 (VDD1), U2.25 (VDDQ1), U2.29 (VDDQ2), U2.37 (VDDQ3), U2.41 (VDDQ4), U2.47 (VDD2), U2.54 (VDD3), U3.4 (VPHY), U3.9 (VPLL), U3.20 (VCCIO), U3.31 (VCCIO), U3.42 (VCCIO), U3.50 (VREGIN), U3.56 (VCCIO), U5.6 (VCC), U6.23 (V_{CCB}), U6.24 (V_{CCB}), U7.23 (V_{CCB}), U7.24 (V_{CCB}), U9.3 (~WP/IO_{2}), U9.7 (~HOLD/~RESET/IO_{3}), U9.8 (VCC), Y2.1 (TRI-STATE), Y2.4 (VDD)
V5: C36.1, C60.1, C70.1, C90.1, J2.15 (VBUS1), J2.16 (VBUS2), U4.5 (VBUS), U8.8 (VCC), U10.1 (EN), U10.4 (VIN), U11.1 (EN), U11.4 (VIN), U12.1 (EN), U12.4 (VIN)
VDRV_A: R52.2, R53.1, U8.1 (OUTA)
VDRV_B: R56.2, R57.1, U8.7 (OUTB)
VFB_A: R51.1, R52.1, U8.2 (INA-)
VFB_B: R55.1, R56.1, U8.6 (INB-)
VIO_A: C31.1, C32.1, D1.5 (VP), D2.5 (VP), R53.2, U6.1 (V_{CCA}), U6.2 (DIR)
VIO_B: C34.1, C35.1, D3.5 (VP), D4.5 (VP), R57.2, U7.1 (V_{CCA}), U7.2 (DIR)
VSET_A: C30.1, R50.2, U8.3 (INA+)
VSET_B: C33.1, R54.2, U8.5 (INB+)

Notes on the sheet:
FPGA
other
SDRAM
USB: USB-C, ESD, FT2232H
config: SPI flash (master SPI boot), FT2232H B programs it
inputs

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
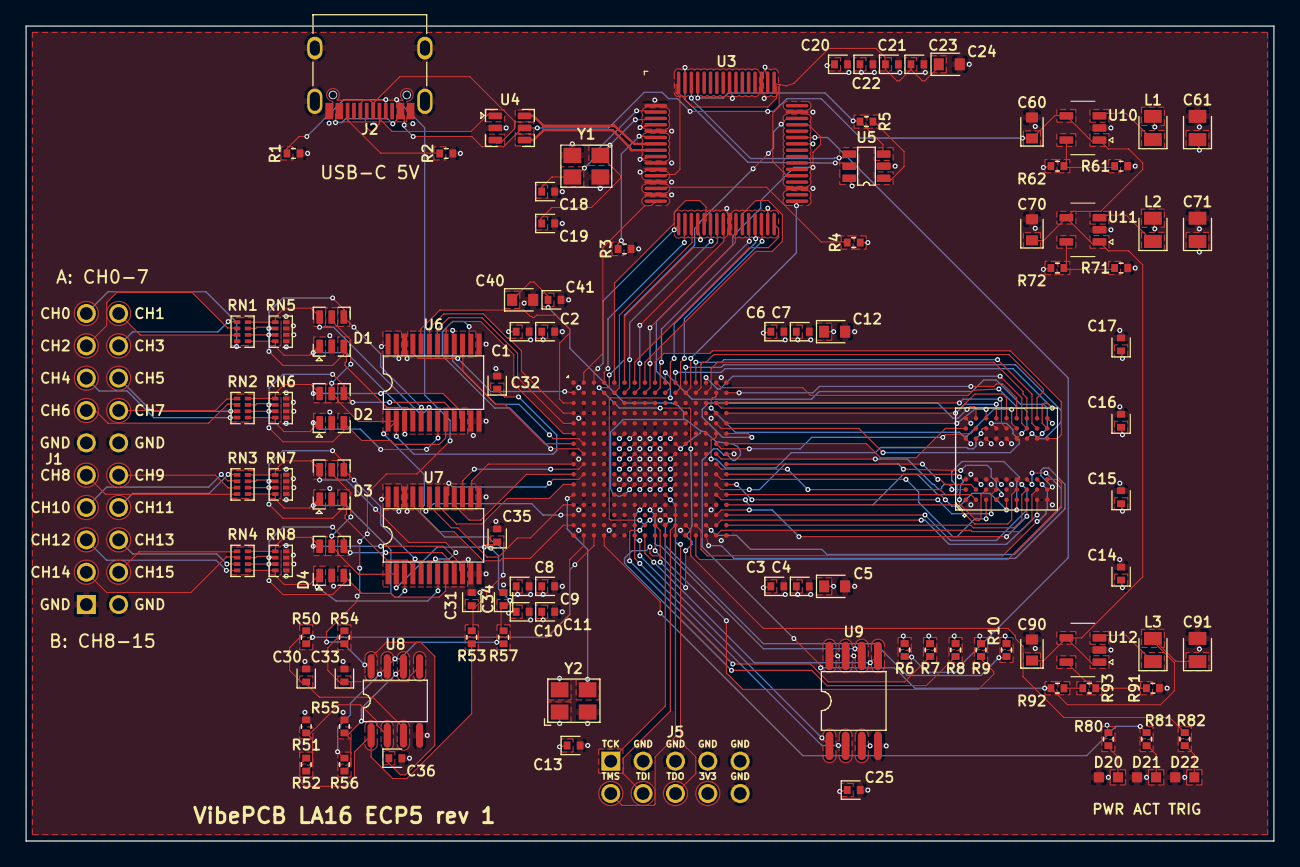
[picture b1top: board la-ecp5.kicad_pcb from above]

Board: 6 copper layers, 98.0 x 64.0 mm, 103 parts (0 on the bottom side), 158 nets.

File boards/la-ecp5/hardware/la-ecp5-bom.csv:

"Qty","Designator","Value","Footprint","MPN","LCSC Part #"
"24","C1,C2,C3,C4,C6,C7,C8,C9,C10,C11,C13,C14,C15,C16,C17,C20,C21,C22,C23,C25,C32,C35,C36,C41","100nF","tscircuit:capacitor_cap0402","","C1525"
"6","C5,C12,C40,C60,C70,C90","10uF","tscircuit:capacitor_cap0603","","C19702"
"2","C18,C19","18pF","tscircuit:capacitor_cap0402","","C1549"
"1","C24","4.7uF","tscircuit:capacitor_cap0603","","C19666"
"4","C30,C31,C33,C34","1uF","tscircuit:capacitor_cap0402","","C52923"
"3","C61,C71,C91","22uF","tscircuit:capacitor_cap0805","","C45783"
"4","D1,D2,D3,D4","SRV05-4","tscircuit:SRV05-4","SRV05-4","C2836319"
"3","D20,D21,D22","KT-0603G","tscircuit:KT-0603G","KT-0603G","C12624"
"1","J1","pin_header_pinrow20_p2_54_nopinlabels_rows2","tscircuit:pin_header_pinrow20_p2_54_nopinlabels_rows2","",""
"1","J2","TYPE-C-31-M-12","tscircuit:TYPE-C-31-M-12","TYPE-C-31-M-12","C165948"
"1","J5","pin_header_pinrow10_p2_54_rows2","tscircuit:pin_header_pinrow10_p2_54_rows2","",""
"3","L1,L2,L3","2.2µH","tscircuit:inductor_0805","","C63167"
"2","R1,R2","5.1kΩ","tscircuit:resistor_res0402","","C25905"
"2","R3,R71","12kΩ","tscircuit:resistor_res0402","","C25752"
"13","R4,R6,R7,R8,R9,R10,R50,R51,R54,R55,R72,R91,R93","10kΩ","tscircuit:resistor_res0402","","C25744"
"1","R5","2.2kΩ","tscircuit:resistor_res0402","","C25879"
"2","R52,R56","20kΩ","tscircuit:resistor_res0402","","C25765"
"2","R53,R57","10Ω","tscircuit:resistor_res0402","","C25077"
"2","R61,R92","22kΩ","tscircuit:resistor_res0402","","C25768"
"1","R62","100kΩ","tscircuit:resistor_res0402","","C25741"
"3","R80,R81,R82","330Ω","tscircuit:resistor_res0402","","C25104"
"4","RN1,RN2,RN3,RN4","4D02WGJ0102TCE","tscircuit:4D02WGJ0102TCE","4D02WGJ0102TCE","C25726"
"4","RN5,RN6,RN7,RN8","RTA02-4D105JTH","tscircuit:RTA02-4D105JTH","RTA02-4D105JTH","C458532"
"1","U1","LFE5U-25F-7BG256I","tscircuit:LFE5U-25F-7BG256I","LFE5U-25F-7BG256I","C1550762"
"1","U2","IS42S16160J-7BLI","tscircuit:IS42S16160J-7BLI","IS42S16160J-7BLI","C1348766"
"1","U3","FT2232HL-REEL","tscircuit:FT2232HL-REEL","FT2232HL-REEL","C27882"
"1","U4","USBLC6-2SC6","tscircuit:USBLC6-2SC6","USBLC6-2SC6","C7519"
"1","U5","93LC56BT-I/OT","tscircuit:93LC56BT-I_OT","93LC56BT-I/OT","C190271"
"2","U6,U7","SN74LVC8T245PWR","tscircuit:SN74LVC8T245PWR","SN74LVC8T245PWR","C27643"
"1","U8","TLV9062IDR","tscircuit:TLV9062IDR","TLV9062IDR","C398355"
"1","U9","W25Q128JVSIQ","tscircuit:W25Q128JVSIQ","W25Q128JVSIQ","C97521"
"3","U10,U11,U12","TLV62569DBVR","tscircuit:TLV62569DBVR","TLV62569DBVR","C141836"
"1","Y1","X322512MSB4SI","tscircuit:X322512MSB4SI","X322512MSB4SI","C9002"
"1","Y2","SX3M100.000B20F30TNN","tscircuit:SX3M100_000B20F30TNN","SX3M100.000B20F30TNN","C5179979"
